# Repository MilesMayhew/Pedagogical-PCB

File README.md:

# Project Title

A brief description of what this project does and who it's for.

## Table of Contents

- [Introduction](#introduction)
- [Installation](#installation)
- [Usage](#usage)
- [Technology Stack](#technology-stack)

## Introduction
The goal of this project is to develop hardware to facilitate a new learning environment for use in ECE3430 (Introduction to Embedded Computer Systems). The board will support the use of two widely used development boards, the STM32 development board and the TI MSPM0 development board, and contain a number of auxiliary I/O that can be used to develop learning activities to learn how to interface to digital I/O, analog I/O, and serial I/O. This includes a complete hardware design and software solutions for specific implementations of learning activities using specific I/O 
## Usage
- **STM32**
  - For each of the provided software solutions: Open STM32CubeIDE and imp# Bill of Materials (BOM)

## Overview

A comprehensive list of all the components required for the project, including specifications and sourcing information.

## Table of Contents

- [Components](#components)
- [Tools Required](#tools-required)
- [Notes](#notes)

## Components

| Item No | Component              | Quantity | Description                   | Supplier/Source         | Part Number       | Price      |
|---------|-----------------------|----------|-------------------------------|-------------------------|-------------------|------------|
| 1       | Resistor              | 10       | 220 Ohm, 1/4 Watt, 5% Tolerance | [Digi-Key](https://www.digikey.com/) | 220R-1/4W-5%       | $0.10     |
| 2       | Capacitor             | 5        | 100 µF, 16V Electrolytic     | [Mouser](https://www.mouser.com/) | 100uF-16V        | $0.25     |
| 3       | Microcontroller       | 1        | ATmega328P                    | [SparkFun](https://www.sparkfun.com/) | ATMEGA328P         | $2.50     |
| 4       | PCB                   | 1        | Custom PCB                    | [JLCPCB](https://www.jlcpcb.com/) | CustomPCB-XYZ      | $3.00     |
| 5       | KiCad Software        | 1        | PCB Design Software           | [KiCad](https://www.kicad.org/) | N/A                 | Free       |

## Tools Required

- Soldering Iron
- Wire Cutters
- Multimeter
- Screwdriver Set

## Notes

- Ensure all components meet the specified requirements.
- Check for component availability and potential substitutions.
ort file as new project. Flash to STM32 development board, and connect correct IO to hardware pins as documented in solution.

## Installation

1. Clone the repository:
   ```bash
   git clone https://github.com/MilesMayhew/Pedagogical-PCB.git
## Technology Stack

- **Languages**: 
  - C
- **Boards**
  - STM32 nucleo
  - TI LP-MSPMOG3507
- **Tools / Libraries**:
  - Git
  - STM32CubeIDE 1.16.0
  - Code Composer Studio
- **Hardware Design**:
  - KiCad

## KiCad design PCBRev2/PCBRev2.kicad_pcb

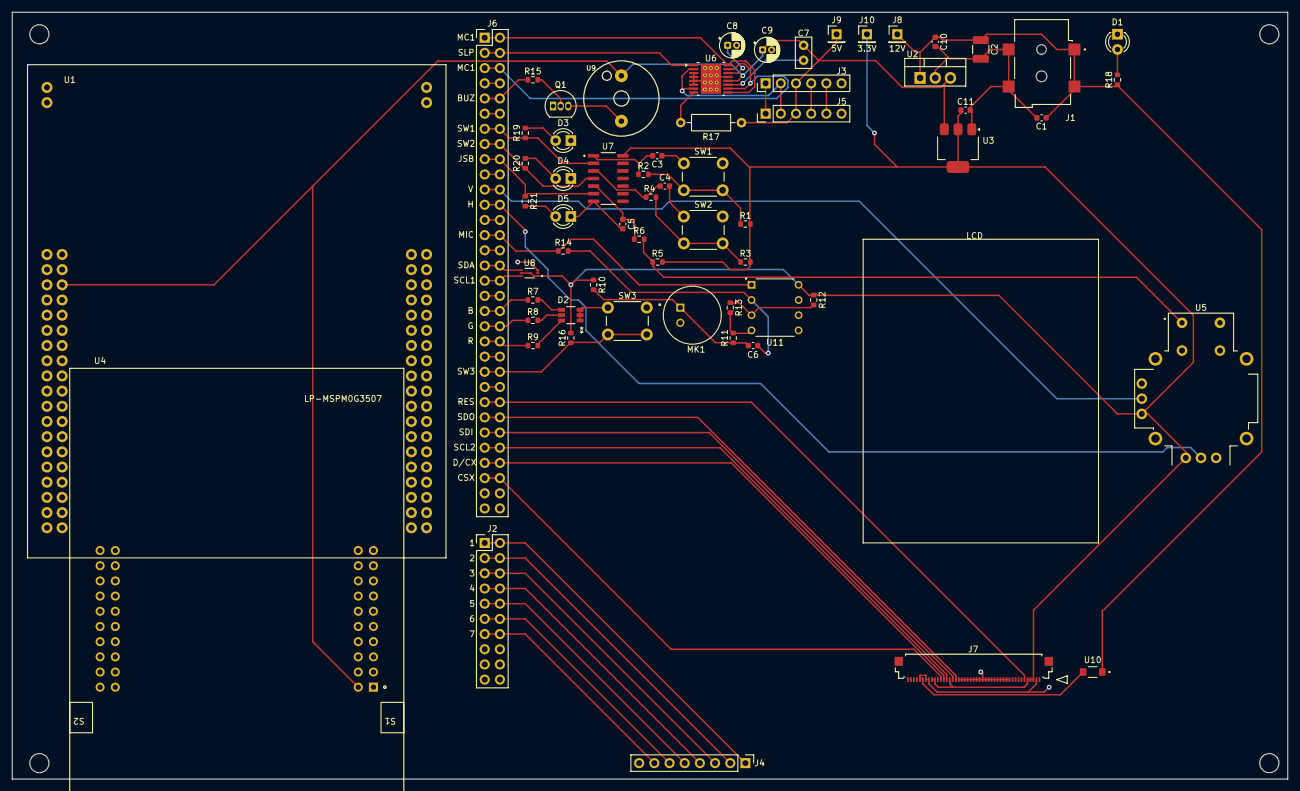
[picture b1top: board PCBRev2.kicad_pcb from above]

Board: 2 copper layers, 213.4 x 128.3 mm, 63 parts (0 on the bottom side), 68 nets.

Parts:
C1: 0.1uf; C_0603_1608Metric
C2: 47uf; C_1210_3225Metric_Pad1.33x2.70mm_HandSolder
C3, C4, C5: 0.47uF; C_0603_1608Metric
C6: 1 uF; C_0603_1608Metric
C7: 0.01 uF; C_Disc_D5.0mm_W2.5mm_P2.50mm
C8: 2.2uF; CP_Radial_D4.0mm_P1.50mm
C9: 10UF; CP_Radial_D4.0mm_P1.50mm
C10: 0.22uf; C_0603_1608Metric
C11: 1uf; C_0603_1608Metric
D1, D3, D4, D5: LED; LED_D3.0mm_FlatTop
D2: AAAF3529LSEEZGKQBKS; LED_AAAF3529LSEEZGKQBKS_KNB
J1: 54-00164; TENSILITY_54-00164
J2: Conn_02x10_Odd_Even; PinHeader_2x10_P2.54mm_Vertical
J3, J5: PinHeader_1x06_P2.54mm_Vertical
J4: Keypad; PinHeader_1x08_P2.54mm_Vertical
J6: Conn_02x30_Odd_Even; PinHeader_2x32_P2.54mm_Vertical
J7: 512964594; CON_512964594_MOL
J8: 12V; PinHeader_1x01_P2.54mm_Vertical
J9: 5V; PinHeader_1x01_P2.54mm_Vertical
J10: 3.3V; PinHeader_1x01_P2.54mm_Vertical
MK1: CMA-4544PF-W; MIC_CMA-4544PF-W
Q1: 2N4401; TO-92_Inline
R1, R2, R3, R4, R5, R6, R16: 10kR; R_0603_1608Metric
R7, R8: 300; R_0603_1608Metric
R9: 750; R_0603_1608Metric
R10, R11, R12, R13: 2.2kR; R_0603_1608Metric
R14: 68k; R_0603_1608Metric
R15: 620; R_0603_1608Metric
R17: 10K; R_Axial_DIN0207_L6.3mm_D2.5mm_P10.16mm_Horizontal
R18: 510; R_0603_1608Metric
R19, R20: 68; R_0603_1608Metric
R21: 330; R_0603_1608Metric
SW1, SW2, SW3: SW_Push; SW_PUSH_6mm_H7.3mm
U1: NUCLEO-G0B1RE; MODULE_NUCLEO-G0B1RE
U2: LM7805_TO220; TO-220-3_Vertical
U3: TLV1117-33; SOT-223-3_TabPin2
U4: LP-MSPM0G3507; ti_LP_MSPM0G3507
U5: COM-09032; XDCR_COM-09032
U6: DRV8833PWP; HTSSOP-16-1EP_4.4x5mm_P0.65mm_EP3.4x5mm_Mask2.46x2.31mm_The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
U7: SN74AHCT14QDRG4Q1; SOIC127P600X175-14N
U8: BH1750FVI-TR; XDCR_BH1750FVI-TR
U9: WST-1205S
U10: AL5809-20QP1-7; SODFL3717X100N
U11: MCP6002-I_P; DIP787W46P254L927H533Q8

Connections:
+5V: C7.1, C9.1, J3.3 (Tach_Power), J5.3 (Tach_Power), J9.1, R17.1, U1.CN7_6 (E5V), U2.3 (VO), U3.3 (VI), U4.J3_1 (+VBUS), U6.12 (VM), U9.+
+12V: C1.1, C2.1, C10.1, J1.A1, J1.A2, J8.1, R18.1, U2.1 (VI), U10.1 (IN)
/Button1 Input: R1.1, R2.2, SW1.2
/Button2 Input: R3.1, R4.2, SW2.2
/Motor_Drive_1: J3.2 (Fan_1), J5.2 (Fan_1), U6.2 (AOUT1), U6.7 (BOUT1)
/Tach_Out_1: J3.4 (Tach_Out_1), J5.4 (Tach_Out_1)
/Tach_Out_2: J3.5 (Tach_Out_2), J5.5 (Tach_Out_2)
/_Motor_Fault: R17.2, U6.8 (~FAULT)
B: J6.37, J6.38, R7.1
ButtonNoDebounce: J6.45, J6.46, R16.1, SW3.2
BuzzerGPIO: J6.9, J6.10, R15.1
CSX: J6.59, J6.60, J7.34
D/CX: J6.57, J6.58, J7.33
G: J6.39, J6.40, R8.1
GNDREF: C1.2, C2.2, C3.1, C4.2, C5.2, C8.2, C9.2, C10.2, C11.2, D1.1 (K), D2.1, D2.2, D2.3, D3.1 (K), D4.1 (K), D5.1 (K), J1.B, J1.C, J3.1 (Fan_2), J3.6 (Tach_GND), J5.1 (Fan_2), J5.6 (Tach_GND), J7.2, J7.11, J7.12, J7.13, J7.14, J7.15, J7.16, J7.17, J7.18, J7.19, J7.20, J7.21, J7.22, J7.23, J7.24, J7.25, J7.26, J7.27, J7.28, J7.38, J7.39, J7.41, MK1.2, Q1.1 (S), R11.2, R13.2, SW1.1, SW2.1, SW3.1, U1.CN7_8 (GND), U1.CN7_19 (GND), U1.CN7_20 (GND), U1.CN7_22 (GND), U1.CN10_20 (GND), U1.JP4_1 (GND), U1.JP4_2 (GND), U1.JP5_1 (GND), U1.JP5_2 (GND), U2.2 (GND), U3.1 (GND), U4.J3_2 (GND), U5.B2A (SEL-), U5.H3 (H-), U5.S1 (SHIELD), U5.S2 (SHIELD), U5.S3 (SHIELD), U5.S4 (SHIELD), U5.V3 (V-), U6.3 (AISEN), U6.4 (AOUT2), U6.5 (BOUT2), U6.6 (BISEN), U6.13 (GND), U6.17 (GND), U7.7 (GND), U8.2 (ADDR), U8.3 (GND), U11.4 (VSS)
H: J6.23, J6.24, U5.H2 (H)
JSB: J6.17, J6.18, R21.1, U7.6 (3Y)
MicOut: J6.27, J6.28, R14.1, U11.1 (VOUTA)
MotorControl1: J6.1, J6.2, U6.9 (BIN1), U6.16 (AIN1)
MotorControl2: J6.5, J6.6, U6.10 (BIN2), U6.15 (AIN2)
Motor_Sleep: J6.3, J6.4, U6.1 (~SLEEP)
unnamed: C6.1, MK1.1, R10.2, R11.1
unnamed: D1.2 (A), R18.2
unnamed: D2.4, R7.2
unnamed: D2.5, R8.2
unnamed: D2.6, R9.2
unnamed: D3.2 (A), R19.2
unnamed: D4.2 (A), R20.2
unnamed: D5.2 (A), R21.2
unnamed: J2.1, J2.2, J4.1
unnamed: J2.3, J2.4, J4.2
unnamed: J2.5, J2.6, J4.3
unnamed: J2.7, J2.8, J4.4
unnamed: J2.9, J2.10, J4.5
unnamed: J2.11, J2.12, J4.6
unnamed: J2.13, J2.14, J4.7
unnamed: J6.7, J6.8
unnamed: J6.11, J6.12
unnamed: J6.19, J6.20
unnamed: J6.25, J6.26
unnamed: J6.29, J6.30
unnamed: J6.35, J6.36
unnamed: J6.43, J6.44
unnamed: J6.47, J6.48
unnamed: Q1.3 (D), U9.-
unnamed: Q1.2 (G), R15.2
unnamed: U1.CN7_12 (3V3), U1.CN7_16 (3V3)
unnamed: U1.CN10_9 (AGND), U1.CN10_32 (AGND)
unnamed: R5.1, R6.2, U5.B1A (SEL+)
unnamed: C7.2, U6.11 (VCP)
unnamed: C8.1, U6.14 (VINT)
unnamed: C3.2, R2.1, U7.1 (1A)
unnamed: C4.1, R4.1, U7.3 (2A)
unnamed: C5.1, R6.1, U7.5 (3A)
unnamed: J7.40, U10.2 (OUT)
unnamed: R12.2, R13.1, U11.3 (VINA+)
unnamed: C6.2, R14.2, U11.2 (VINA-)
R: J6.41, J6.42, R9.1
RESX: J6.49, J6.50, J7.6
SCL: J6.55, J6.56, J7.32
SCLlight: J6.33, J6.34, U8.6 (SCL)
SDA: J6.31, J6.32, U8.4 (SDA)
SDI: J6.53, J6.54, J7.30
SDO: J6.51, J6.52, J7.29
SW1: J6.13, J6.14, R19.1, U7.2 (1Y)
SW2: J6.15, J6.16, R20.1, U7.4 (2Y)
V: J6.21, J6.22, U5.V2 (V)
VDD: C11.1, J7.3, J7.4, J7.5, J7.31, J7.36, J7.37, J10.1, R1.2, R3.2, R5.2, R10.1, R12.1, R16.2, U3.2 (VO), U5.H1 (H+), U5.V1 (V+), U7.14 (VCC), U8.1 (VCC), U8.5 (DVI), U11.8 (VDD)

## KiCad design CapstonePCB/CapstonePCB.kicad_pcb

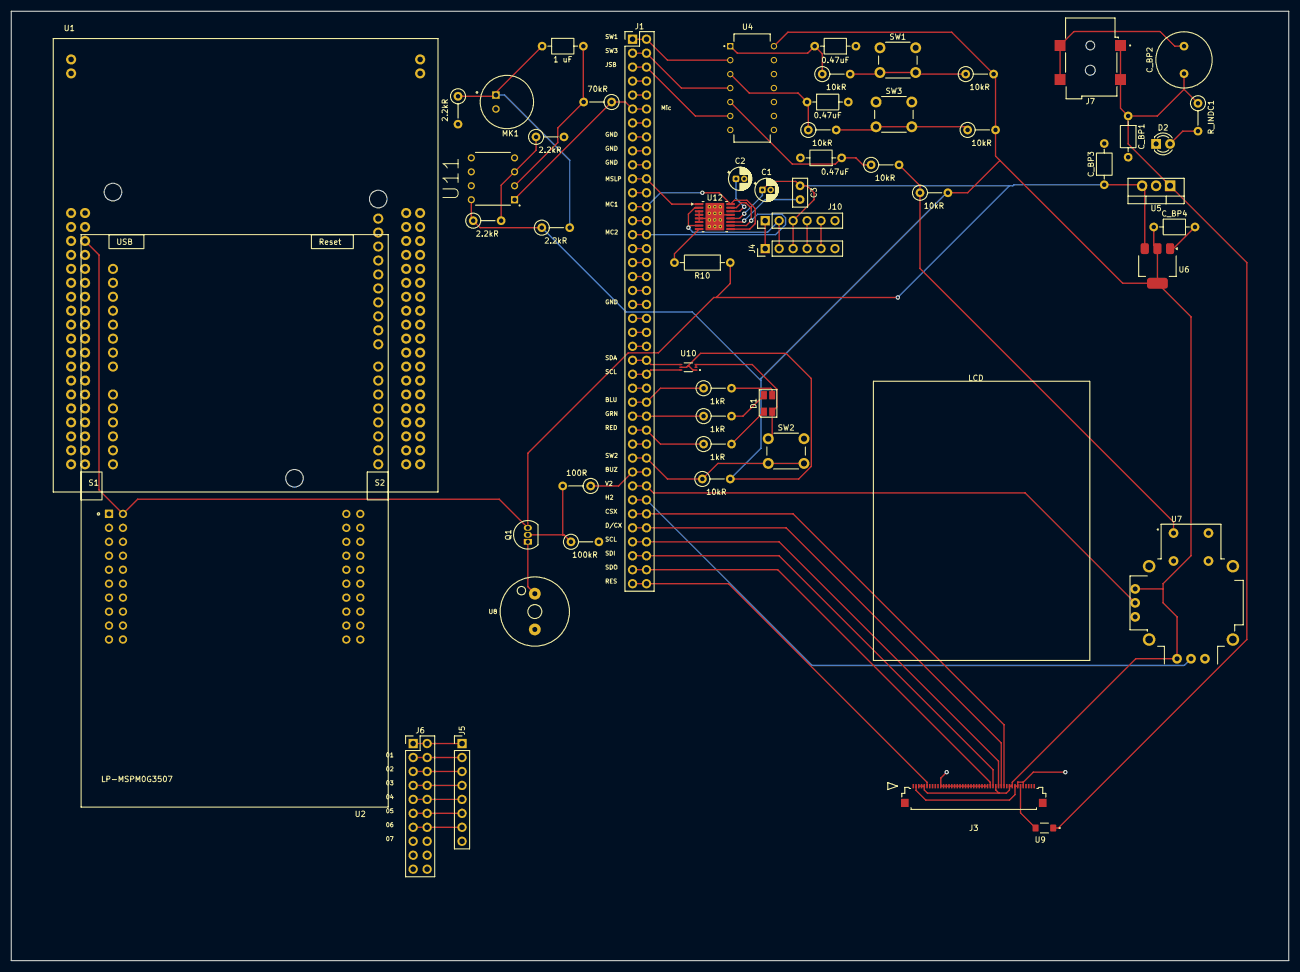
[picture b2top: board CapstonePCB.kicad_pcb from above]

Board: 2 copper layers, 232.4 x 172.7 mm, 55 parts (0 on the bottom side), 93 nets.

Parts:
C1: 10UF; CP_Radial_D4.0mm_P1.50mm
C2: 2.2uF; CP_Radial_D4.0mm_P1.50mm
C3: 0.01 uF; C_Disc_D5.0mm_W2.5mm_P2.50mm
CJS1: 0.47uF; C_Axial_L3.8mm_D2.6mm_P7.50mm_Horizontal
CSW1, CSW3: 0.47uF; C_Axial_L3.8mm_D2.6mm_P7.50mm_Horizontal
C_BP1: 0.1 uf; C_Axial_L3.8mm_D2.6mm_P7.50mm_Horizontal
C_BP2: 47 uf; C_Radial_D10.0mm_H20.0mm_P5.00mm
C_BP3, C_BP4: 100 uf; C_Axial_L3.8mm_D2.6mm_P7.50mm_Horizontal
C_s2: 1 uF; C_Axial_L3.8mm_D2.6mm_P7.50mm_Horizontal
D1: ASMB-MTB1-0A3A2; LED_Avago_PLCC4_3.2x2.8mm_CW
D2: LED; LED_D3.0mm_FlatTop
J1: Conn_02x40_Counter_Clockwise; PinHeader_2x40_P2.54mm_Vertical
J3: 512964594; CON_512964594_MOL
J4, J10: PinHeader_1x06_P2.54mm_Vertical
J5: Keypad; PinHeader_1x08_P2.54mm_Vertical
J6: Conn_02x10_Odd_Even; PinHeader_2x10_P2.54mm_Vertical
J7: 54-00164; TENSILITY_54-00164
MK1: CMA-4544PF-W; MIC_CMA-4544PF-W
PullUpResistor2: 10kR; R_Axial_DIN0207_L6.3mm_D2.5mm_P5.08mm_Vertical
PullUpResistorJS1: 10kR; R_Axial_DIN0207_L6.3mm_D2.5mm_P5.08mm_Vertical
PullUpResistorSW1, PullUpResistorSW3: 10kR; R_Axial_DIN0207_L6.3mm_D2.5mm_P5.08mm_Vertical
Q1: 2N7000; TO-92_Inline
R10: 10K; R_Axial_DIN0207_L6.3mm_D2.5mm_P10.16mm_Horizontal
RJS1: 10kR; R_Axial_DIN0207_L6.3mm_D2.5mm_P5.08mm_Vertical
RSW1, RSW3: 10kR; R_Axial_DIN0207_L6.3mm_D2.5mm_P5.08mm_Vertical
R_BUZ1: 100R; R_Axial_DIN0207_L6.3mm_D2.5mm_P5.08mm_Vertical
R_BUZ2: 100kR; R_Axial_DIN0207_L6.3mm_D2.5mm_P5.08mm_Vertical
R_COFF2, R_COFF3, R_COFF4: 1kR; R_Axial_DIN0207_L6.3mm_D2.5mm_P5.08mm_Vertical
R_INDC1: 5.5k ohm; R_Axial_DIN0207_L6.3mm_D2.5mm_P5.08mm_Vertical
R_SNSA2, R_SNSA3, R_SNSA5, R_SNSA6: 2.2kR; R_Axial_DIN0207_L6.3mm_D2.5mm_P5.08mm_Vertical
R_SNSA4: 70kR; R_Axial_DIN0207_L6.3mm_D2.5mm_P5.08mm_Vertical
SW1, SW2, SW3: SW_Push; SW_PUSH_6mm_H7.3mm
U1: NUCLEO-G0B1RE; MODULE_NUCLEO-G0B1RE
U2: LP-MSPM0G3507; ti_LP_MSPM0G3507
U4: SN74AHC14N; DIP794W45P254L1969H508Q14
U5: LM7805_TO220; TO-220-3_Vertical
U6: TLV1117-33; SOT-223-3_TabPin2
U7: COM-09032; XDCR_COM-09032
U8: WST-1205S
U9: AL5809-20QP1-7; SODFL3717X100N
U10: BH1750FVI-TR; XDCR_BH1750FVI-TR
U11: MCP6002-I_P; DIP787W46P254L927H533Q8
U12: DRV8833PWP; HTSSOP-16-1EP_4.4x5mm_P0.65mm_EP3.4x5mm_Mask2.46x2.31mm_The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

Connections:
+3.3V: U1.CN6_2 (3V3), U1.CN6_4 (3V3), U1.CN7_12 (3V3), U1.CN7_16 (3V3)
+5V: C1.1, C3.1, C_BP3.1, J4.3 (Tach_Power), J10.3 (Tach_Power), Q1.3 (D), R10.1, U1.CN7_6 (E5V), U2.J3_1 (+VBUS), U5.3 (VO), U6.3 (VI), U12.12 (VM)
+12V: C_BP1.1, C_BP2.1, J7.A1, J7.A2, R_INDC1.1, U5.1 (VI), U9.1 (IN)
/Button1 Input: PullUpResistorSW1.1, RSW1.2, SW1.2
/Button2 Input: PullUpResistorSW3.1, RSW3.2, SW3.2
/Button No Debouning: J1.61, J1.62, PullUpResistor2.1, SW2.2
/Motor_Drive_1: J4.2 (Fan_1), J10.2 (Fan_1), U12.2 (AOUT1), U12.7 (BOUT1)
/Tach_Out_1: J4.4 (Tach_Out_1), J10.4 (Tach_Out_1)
/Tach_Out_2: J4.5 (Tach_Out_2), J10.5 (Tach_Out_2)
/_Motor_Fault: R10.2, U12.8 (~FAULT)
BuzzerGPIO: J1.63, J1.64, R_BUZ1.1
GNDREF: C1.2, C2.2, CJS1.2, CSW1.1, CSW3.2, C_BP1.2, C_BP2.2, C_BP3.2, C_BP4.2, D1.4 (A), D2.1 (K), J1.15, J1.16, J1.17, J1.18, J1.19, J1.20, J1.27, J1.28, J1.39, J1.40, J3.2, J3.11, J3.12, J3.13, J3.14, J3.15, J3.16, J3.17, J3.18, J3.19, J3.20, J3.21, J3.22, J3.23, J3.24, J3.25, J3.26, J3.27, J3.28, J3.38, J3.39, J3.41, J4.1 (Fan_2), J4.6 (Tach_GND), J7.B, J7.C, J10.1 (Fan_2), J10.6 (Tach_GND), MK1.2, R_BUZ2.2, R_SNSA3.2, R_SNSA6.2, SW1.1, SW2.1, SW3.1, U1.CN6_6 (GND), U1.CN6_7 (GND), U1.CN7_8 (GND), U1.CN7_19 (GND), U1.CN7_20 (GND), U1.CN7_22 (GND), U1.CN10_20 (GND), U1.JP4_1 (GND), U1.JP4_2 (GND), U1.JP5_1 (GND), U1.JP5_2 (GND), U2.J3_2 (GND), U4.7 (GND), U5.2 (GND), U6.1 (GND), U7.B2A (SEL-), U7.H3 (H-), U7.S1 (SHIELD), U7.S2 (SHIELD), U7.S3 (SHIELD), U7.S4 (SHIELD), U7.V3 (V-), U8.-, U10.2 (ADDR), U10.3 (GND), U11.4 (VSS), U12.3 (AISEN), U12.4 (AOUT2), U12.5 (BOUT2), U12.6 (BISEN), U12.13 (GND), U12.17 (GND)
MicOut: J1.11, J1.12, R_SNSA4.1, U11.1 (VOUTA)
MotorControl1: J1.25, J1.26, U12.9 (BIN1), U12.16 (AIN1)
MotorControl2: J1.29, J1.30, U12.10 (BIN2), U12.15 (AIN2)
Motor_Sleep: J1.21, J1.22, U12.1 (~SLEEP)
unnamed: C_s2.1, MK1.1, R_SNSA2.2, R_SNSA3.1
unnamed: D1.3 (BK), R_COFF4.2
unnamed: D1.2 (GK), R_COFF3.2
unnamed: D1.1 (RK), R_COFF2.2
unnamed: D2.2 (A), R_INDC1.2
unnamed: J1.1, J1.2, U4.2 (1Y)
unnamed: J1.3, J1.4, U4.4 (2Y)
unnamed: J1.5, J1.6, U4.6 (3Y)
unnamed: J1.7, J1.8
unnamed: J1.9, J1.10
unnamed: J1.13, J1.14
unnamed: J1.23, J1.24
unnamed: J1.31, J1.32
unnamed: J1.33, J1.34
unnamed: J1.35, J1.36
unnamed: J1.37, J1.38
unnamed: J1.41, J1.42
unnamed: J1.43, J1.44
unnamed: J1.45, J1.46
unnamed: J1.47, J1.48, U10.4 (SDA)
unnamed: J1.49, J1.50, U10.6 (SCL)
unnamed: J1.51, J1.52
unnamed: J1.53, J1.54, R_COFF4.1
unnamed: J1.55, J1.56, R_COFF3.1
unnamed: J1.57, J1.58, R_COFF2.1
unnamed: J1.59, J1.60
unnamed: J1.65, J1.66, U7.V2 (V)
unnamed: J1.67, J1.68, U7.H2 (H)
unnamed: J1.69, J1.70, J3.34
unnamed: J1.71, J1.72, J3.33
unnamed: J1.73, J1.74, J3.32
unnamed: J1.75, J1.76, J3.30
unnamed: J1.77, J1.78, J3.29
unnamed: J1.79, J1.80, J3.6
unnamed: J5.1, J6.1, J6.2
unnamed: J5.2, J6.3, J6.4
unnamed: J5.3, J6.5, J6.6
unnamed: J5.4, J6.7, J6.8
unnamed: J5.5, J6.9, J6.10
unnamed: J5.6, J6.11, J6.12
unnamed: J5.7, J6.13, J6.14
unnamed: Q1.2 (G), R_BUZ1.2, R_BUZ2.1
unnamed: Q1.1 (S), U8.+
unnamed: U1.CN7_28 (PA0), U1.CN8_1 (PA0)
unnamed: U1.CN7_30 (PA1), U1.CN8_2 (PA1)
unnamed: U1.CN7_32 (PA4), U1.CN8_3 (PA4)
unnamed: U1.CN5_6 (PA5), U1.CN10_11 (PA5)
unnamed: U1.CN5_5 (PA6), U1.CN10_13 (PA6)
unnamed: U1.CN5_4 (PA7), U1.CN10_15 (PA7)
unnamed: U1.CN9_8 (PA8), U1.CN10_23 (PA8)
unnamed: U1.CN5_1 (PA9), U1.CN10_21 (PA9)
unnamed: U1.CN9_3 (PA10), U1.CN10_33 (PA10)
unnamed: U1.CN5_3 (PB0), U1.CN10_17 (PB0)
unnamed: U1.CN7_34 (PB1), U1.CN8_4 (PB1)
unnamed: U1.CN9_4 (PB3), U1.CN10_31 (PB3)
unnamed: U1.CN9_6 (PB4), U1.CN10_27 (PB4)
unnamed: U1.CN9_5 (PB5), U1.CN10_29 (PB5)
unnamed: U1.CN5_10 (PB8), U1.CN10_3 (PB8)
unnamed: U1.CN5_9 (PB9), U1.CN10_5 (PB9)
unnamed: U1.CN9_7 (PB14), U1.CN10_25 (PB14)
unnamed: U1.CN9_2 (PC4), U1.CN10_35 (PC4)
unnamed: U1.CN9_1 (PC5), U1.CN10_37 (PC5)
unnamed: U1.CN5_2 (PC7), U1.CN10_19 (PC7)
unnamed: U1.CN6_3 (~RST), U1.CN7_14 (~RST)
unnamed: U1.CN6_5 (5V), U1.CN7_18 (5V)
unnamed: U1.CN5_7 (AGND), U1.CN10_9 (AGND), U1.CN10_32 (AGND)
unnamed: U1.CN6_8 (VIN), U1.CN7_24 (VIN)
unnamed: CSW1.2, RSW1.1, U4.1 (1A)
unnamed: CSW3.1, RSW3.1, U4.3 (2A)
unnamed: CJS1.1, RJS1.1, U4.5 (3A)
unnamed: PullUpResistorJS1.1, RJS1.2, U7.B1A (SEL+)
unnamed: J3.40, U9.2 (OUT)
unnamed: R_SNSA5.2, R_SNSA6.1, U11.3 (VINA+)
unnamed: C_s2.2, R_SNSA4.2, U11.2 (VINA-)
unnamed: C3.2, U12.11 (VCP)
unnamed: C2.1, U12.14 (VINT)
VDD: C_BP4.1, J3.3, J3.4, J3.5, J3.31, J3.36, J3.37, PullUpResistor2.2, PullUpResistorJS1.2, PullUpResistorSW1.2, PullUpResistorSW3.2, R_SNSA2.1, R_SNSA5.1, U4.14 (VCC), U6.2 (VO), U7.H1 (H+), U7.V1 (V+), U10.1 (VCC), U10.5 (DVI), U11.8 (VDD)

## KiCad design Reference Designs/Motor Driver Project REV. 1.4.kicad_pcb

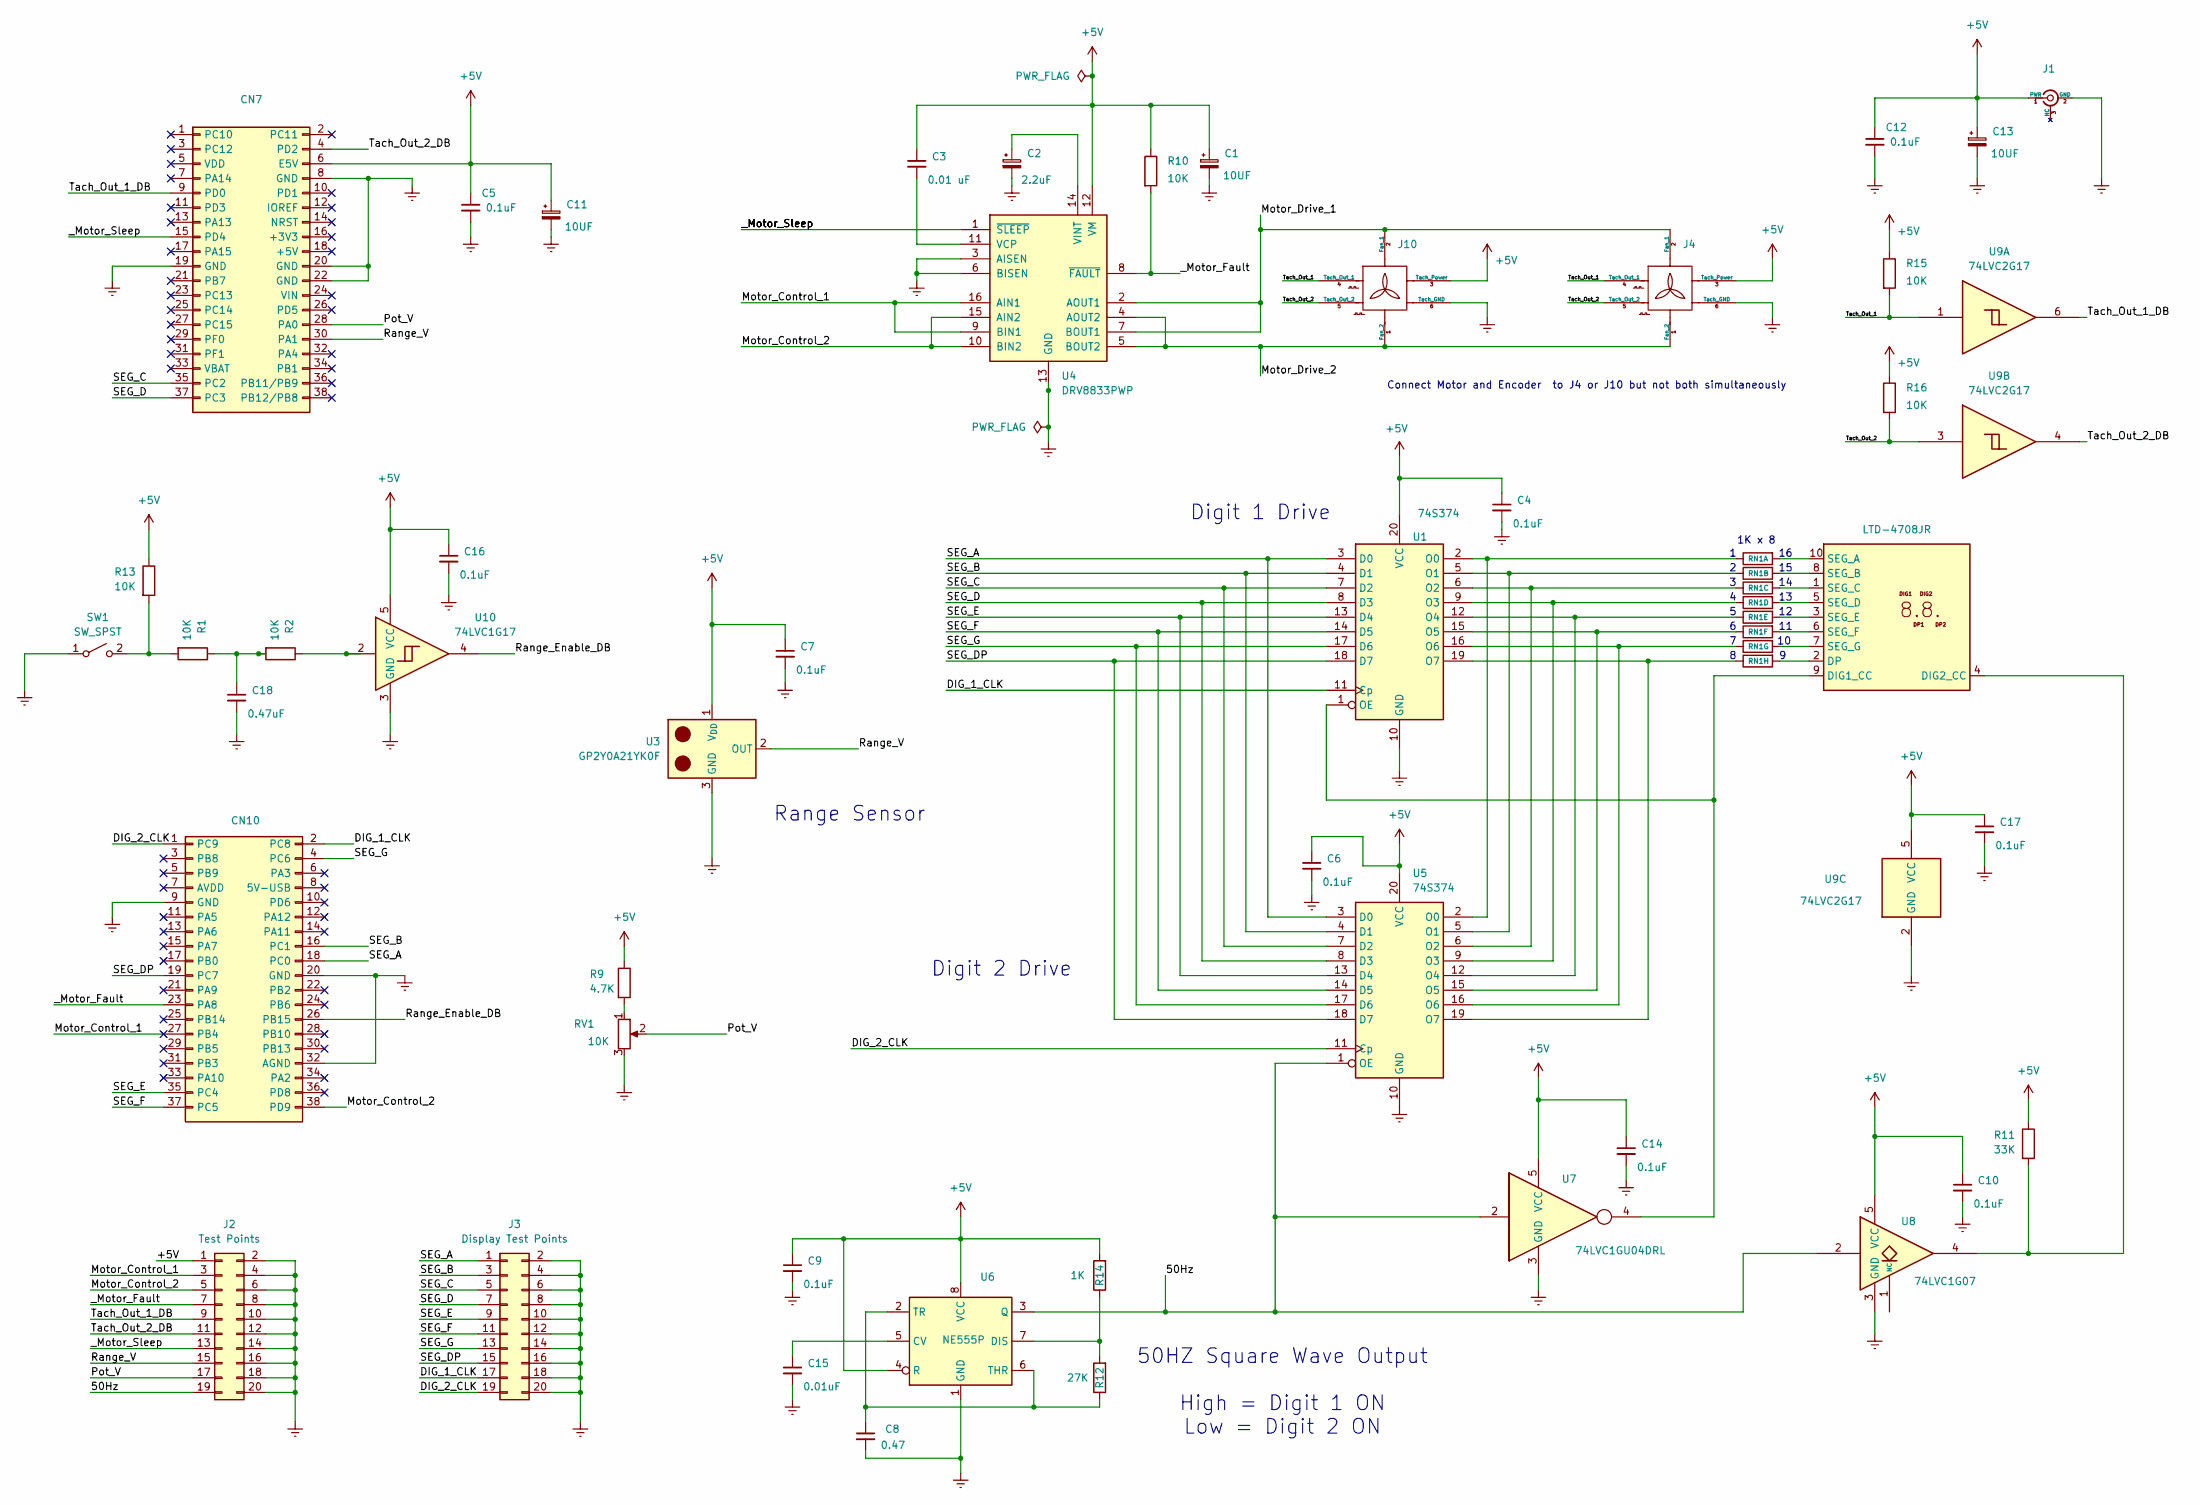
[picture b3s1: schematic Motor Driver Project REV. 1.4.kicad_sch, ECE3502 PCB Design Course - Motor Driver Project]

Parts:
C1, C11, C13: 10UF; CP_Radial_D4.0mm_P1.50mm
C2: 2.2uF; CP_Radial_D4.0mm_P1.50mm
C3: 0.01 uF; C_Disc_D5.0mm_W2.5mm_P2.50mm
C4, C5, C6, C7, C9, C10, C12, C14, C16, C17: 0.1uF; C_Disc_D5.0mm_W2.5mm_P2.50mm
C8: 0.47; C_Disc_D5.0mm_W2.5mm_P2.50mm
C15: 0.01uF; C_Disc_D5.0mm_W2.5mm_P2.50mm
C18: 0.47uF; C_Disc_D5.0mm_W2.5mm_P2.50mm
CN7: Conn_2Rows-38Pins_CN7; PinSocket_2x19_P2.54mm_Vertical_CN7
CN10: Conn_2Rows-38Pins_CN10; PinSocket_2x19_P2.54mm_Vertical_CN10
J1: Conn_Coaxial_3_Pin; BarrelJack_GCT_DCJ200-10-A_Horizontal
J2: Test Points; PinHeader_2x10_P2.54mm_Vertical
J3: Display Test Points; PinHeader_2x10_P2.54mm_Vertical
J4, J10: PinHeader_1x06_P2.54mm_Vertical
R1, R2, R10, R13, R15, R16: 10K; R_Axial_DIN0207_L6.3mm_D2.5mm_P10.16mm_Horizontal
R9: 4.7K; R_Axial_DIN0207_L6.3mm_D2.5mm_P10.16mm_Horizontal
R11: 33K; R_Axial_DIN0207_L6.3mm_D2.5mm_P10.16mm_Horizontal
R12: 27K; R_Axial_DIN0207_L6.3mm_D2.5mm_P10.16mm_Horizontal
R14: 1K; R_Axial_DIN0207_L6.3mm_D2.5mm_P10.16mm_Horizontal
RN1: R_Pack08_Split; DIP-16_W7.62mm
RV1: 10K; TRIM_COM-09806
SW1: SW_SPST; SW2_GF-123-0054_CWI
U1, U5: 74S374; DIP-20_W7.62mm_Socket
U2: LTD-4708JR; 7SegmentLED_LTD-4708JR
U3: GP2Y0A21YK0F; PinHeader_1x03_P2.54mm_Vertical
U4: DRV8833PWP; HTSSOP-16-1EP_4.4x5mm_P0.65mm_EP3.4x5mm_Mask2.46x2.31mm_The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
U6: NE555P; DIP-8_W7.62mm
U7: 74LVC1GU04DRL; SOT-23-5_HandSoldering
U8: 74LVC1G07; SOT-23-5_HandSoldering
U9: 74LVC2G17; SOT-23-6
U10: 74LVC1G17; SOT-23-5

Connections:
+5V: C1.1, C3.1, C4.1, C5.1, C6.1, C7.1, C9.1, C10.1, C11.1, C12.1, C13.1, C14.1, C16.1, C17.1, CN7.6 (E5V), J1.1 (PWR), J2.1, J4.3 (Tach_Power), J10.3 (Tach_Power), R9.1, R10.1, R11.1, R13.1, R14.2, R15.1, R16.1, U1.20 (VCC), U3.1 (V_{DD}), U4.12 (VM), U5.20 (VCC), U6.4 (R), U6.8 (VCC), U7.5 (VCC), U8.5 (VCC), U9.5 (VCC), U10.5 (VCC)
/50Hz: J2.19, U5.1 (OE), U6.3 (Q), U7.2, U8.2
/DIG_1_CLK: CN10.2 (PC8), J3.17, U1.11 (Cp)
/DIG_2_CLK: CN10.1 (PC9), J3.19, U5.11 (Cp)
/Motor_Control_1: CN10.27 (PB4), J2.3, U4.9 (BIN1), U4.16 (AIN1)
/Motor_Control_2: CN10.38 (PD9), J2.5, U4.10 (BIN2), U4.15 (AIN2)
/Motor_Drive_1: J4.2 (Fan_1), J10.2 (Fan_1), U4.2 (AOUT1), U4.7 (BOUT1)
/Motor_Drive_2: J4.1 (Fan_2), J10.1 (Fan_2), U4.4 (AOUT2), U4.5 (BOUT2)
/Pot_V: CN7.28 (PA0), J2.17, RV1.2
/Range_Enable_DB: CN10.26 (PB15), U10.4
/Range_V: CN7.30 (PA1), J2.15, U3.2 (OUT)
/SEG_A: CN10.18 (PC0), J3.1, U1.3 (D0), U5.3 (D0)
/SEG_B: CN10.16 (PC1), J3.3, U1.4 (D1), U5.4 (D1)
/SEG_C: CN7.35 (PC2), J3.5, U1.7 (D2), U5.7 (D2)
/SEG_D: CN7.37 (PC3), J3.7, U1.8 (D3), U5.8 (D3)
/SEG_DP: CN10.19 (PC7), J3.15, U1.18 (D7), U5.18 (D7)
/SEG_E: CN10.35 (PC4), J3.9, U1.13 (D4), U5.13 (D4)
/SEG_F: CN10.37 (PC5), J3.11, U1.14 (D5), U5.14 (D5)
/SEG_G: CN10.4 (PC6), J3.13, U1.17 (D6), U5.17 (D6)
/Tach_Out_1: J4.4 (Tach_Out_1), J10.4 (Tach_Out_1), R15.2, U9.1
/Tach_Out_1_DB: CN7.9 (PD0), J2.9, U9.6
/Tach_Out_2: J4.5 (Tach_Out_2), J10.5 (Tach_Out_2), R16.2, U9.3
/Tach_Out_2_DB: CN7.4 (PD2), J2.11, U9.4
/_Motor_Fault: CN10.23 (PA8), J2.7, R10.2, U4.8 (~FAULT)
/_Motor_Sleep: CN7.15 (PD4), J2.13, U4.1 (~SLEEP)
Earth: C1.2, C2.2, C4.2, C5.2, C6.2, C7.2, C8.2, C9.2, C10.2, C11.2, C12.2, C13.2, C14.2, C15.2, C16.2, C17.2, C18.2, CN7.8 (GND), CN7.19 (GND), CN7.20 (GND), CN7.22 (GND), CN10.9 (GND), CN10.20 (GND), CN10.32 (AGND), J1.2 (GND), J2.2, J2.4, J2.6, J2.8, J2.10, J2.12, J2.14, J2.16, J2.18, J2.20, J3.2, J3.4, J3.6, J3.8, J3.10, J3.12, J3.14, J3.16, J3.18, J3.20, J4.6 (Tach_GND), J10.6 (Tach_GND), RV1.3, SW1.1 (A), U1.10 (GND), U3.3 (GND), U4.3 (AISEN), U4.6 (BISEN), U4.13 (GND), U4.17 (GND), U5.10 (GND), U6.1 (GND), U7.3 (GND), U8.3 (GND), U9.2 (GND), U10.3 (GND)
unnamed: C18.1, R1.1, R2.2
unnamed: R2.1, U10.2
unnamed: R9.2, RV1.1
unnamed: RN1.1 (R1.1), U1.2 (O0), U5.2 (O0)
unnamed: RN1.16 (R1.2), U2.10 (SEG_A)
unnamed: RN1.2 (R2.1), U1.5 (O1), U5.5 (O1)
unnamed: RN1.15 (R2.2), U2.8 (SEG_B)
unnamed: RN1.3 (R3.1), U1.6 (O2), U5.6 (O2)
unnamed: RN1.14 (R3.2), U2.1 (SEG_C)
unnamed: RN1.4 (R4.1), U1.9 (O3), U5.9 (O3)
unnamed: RN1.13 (R4.2), U2.5 (SEG_D)
unnamed: RN1.5 (R5.1), U1.12 (O4), U5.12 (O4)
unnamed: RN1.12 (R5.2), U2.3 (SEG_E)
unnamed: RN1.6 (R6.1), U1.15 (O5), U5.15 (O5)
unnamed: RN1.11 (R6.2), U2.6 (SEG_F)
unnamed: RN1.7 (R7.1), U1.16 (O6), U5.16 (O6)
unnamed: RN1.10 (R7.2), U2.7 (SEG_G)
unnamed: RN1.8 (R8.1), U1.19 (O7), U5.19 (O7)
unnamed: RN1.9 (R8.2), U2.2 (DP)
unnamed: R1.2, R13.2, SW1.2 (B)
unnamed: U1.1 (OE), U2.9 (DIG1_CC), U7.4
unnamed: R11.2, U2.4 (DIG2_CC), U8.4
unnamed: C3.2, U4.11 (VCP)
unnamed: C2.1, U4.14 (VINT)
unnamed: C15.1, U6.5 (CV)
unnamed: R12.2, R14.1, U6.7 (DIS)
unnamed: C8.1, R12.1, U6.2 (TR), U6.6 (THR)

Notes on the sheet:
Range Sensor
50HZ Square Wave Output High = Digit 1 ON Low = Digit 2 ON
Digit 1 Drive
Connect Motor and Encoder to J4 or J10 but not both simultaneously
Digit 2 Drive
1K x 8

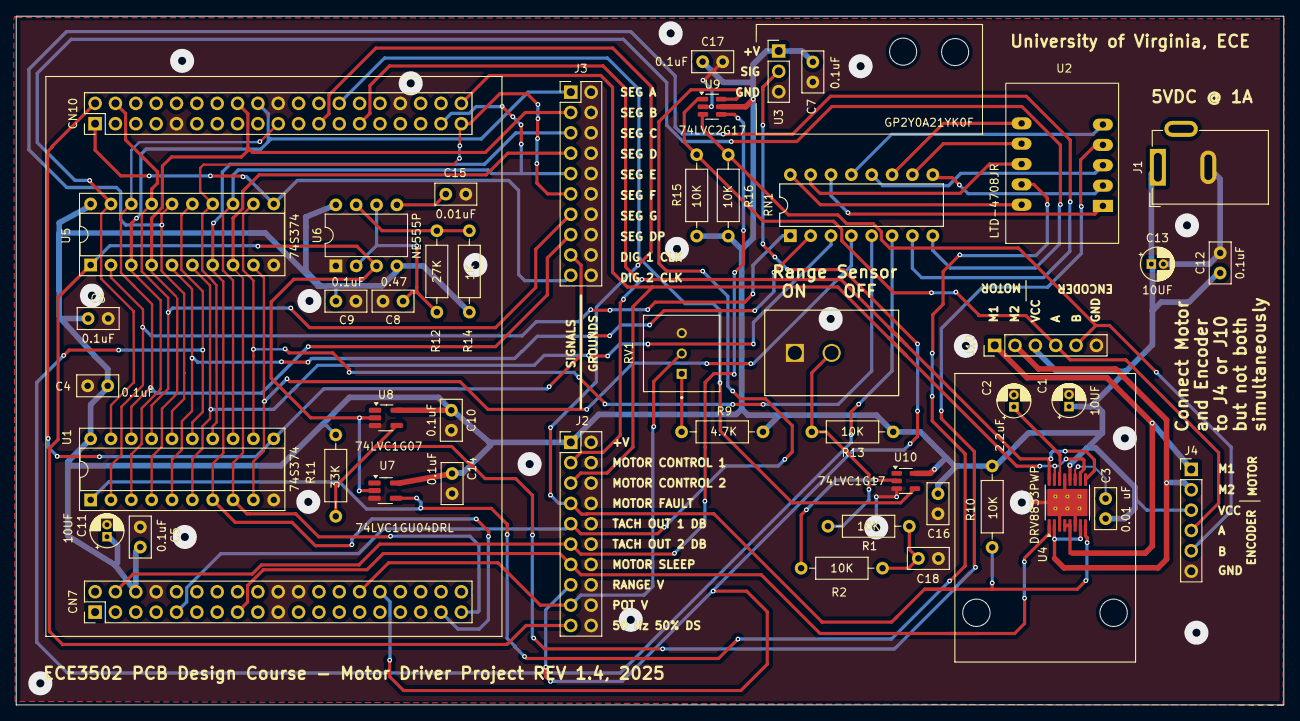
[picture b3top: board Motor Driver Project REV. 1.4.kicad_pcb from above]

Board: 2 copper layers, 158.2 x 86.0 mm, 48 parts (0 on the bottom side), 53 nets.

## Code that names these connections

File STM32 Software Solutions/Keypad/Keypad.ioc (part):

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Mcu.Name=STM32G071R(6-8-B)Tx
Mcu.Package=LQFP64
Mcu.UserName=STM32G071RBTx
PA10.Signal=GPIO_Output
PA13.Mode=Serial_Wire
PA13.Signal=SYS_SWDIO
PA14-BOOT0.Mode=Serial_Wire
PA14-BOOT0.Signal=SYS_SWCLK
PA2.Mode=Asynchronous
PA2.Signal=USART2_TX
PA3.Mode=Asynchronous
PA3.Signal=USART2_RX
PB14.Signal=GPIO_Output
PB3.Signal=GPIO_Input
PB4.Signal=GPIO_Input
PB5.Signal=GPIO_Output
PC4.Signal=GPIO_Input
PC5.Signal=GPIO_Input
RCC.HSE_VALUE=8000000
RCC.SYSCLKFreq_VALUE=16000000
board=custom

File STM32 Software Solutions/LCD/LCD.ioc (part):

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Mcu.Name=STM32G071R(6-8-B)Tx
Mcu.Package=LQFP64
Mcu.UserName=STM32G071RBTx
PA1.Mode=Full_Duplex_Master
PA1.Signal=SPI1_SCK
PA2.Mode=Full_Duplex_Master
PA2.Signal=SPI1_MOSI
PA6.Mode=Full_Duplex_Master
PA6.Signal=SPI1_MISO
PC4.Signal=GPIO_Output
PC5.Signal=GPIO_Output
PC7.Signal=GPIO_Output
RCC.HSE_VALUE=8000000
RCC.SYSCLKFreq_VALUE=16000000
board=custom

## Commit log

2025-09-23 Updated title on silkscreen
2025-09-23 Test commit
2025-09-29 Added MSPM0 outline to schematic.
2025-10-02 Added a barrel jack for connection to wall power.
2025-10-03 Added README
2025-10-03 Added Bill of Materals and reference designs
2025-10-03 Rename 12V_wall_power_datasheet.pdf to IO Component Datasheets/12V_wall_power_datasheet.pdf
2025-10-03 Added barrel jack connector
2025-10-03 Rename 3845_Web.pdf to IO Component Datasheets/Keypad_datasheet
2025-10-03 Rename Keypad_datasheet to Keypad_datasheet
2025-10-03 Rename 858_Web.pdf to IO Component Datasheets/Motor_datasheet
2025-10-03 Rename COM-09032_Web.pdf to IO Component Datasheets/Joystick_datasheet
2025-10-03 Rename ENG_DS_ALCOSWITCH_Push_Button_Switch_IPE_Series_B (1).pdf to IO Component Datasheets/ALCOSWITCH_Push_Button_Switch_datasheet
2025-10-03 Rename Microphone_datasheet.pdf to IO Component Datasheets/Microphone_datasheet.pdf
2025-10-03 Rename NHD-2.4-240320DA-CTXN.pdf to IO Component Datasheets/LCD Datasheet
2025-10-03 Rename RP_3502_datasheet.pdf to IO Component Datasheets/RP_Pushbutton_datasheet.pdf
2025-10-03 Rename SP-1504-June-2018.pdf to IO Component Datasheets/Speaker_datasheet
2025-10-03 Rename WT-1205-16-Feb-2019 (1).pdf to IO Component Datasheets/Buzzer_datasheet
2025-10-03 Rename d6.pdf to IO Component Datasheets/d6_Pushbutton_datasheet
2025-10-03 Updated spacing for headers
2025-10-03 Added Driver Datasheet
2025-10-03 Rename slau873d.pdf to IO Component Datasheets/TI_datasheet
2025-10-03 Updated formating for stm32
2025-10-03 Added motor driver to schematic
2025-10-03 Routed connections for header pins
2025-10-03 Added by-pass capacitors
2025-10-05 Added RC filter + schmitt trigger
2025-10-05 Added LDOs for 5v and 3.3v rails
2025-10-05 Added RGB led to schematic
2025-10-05 Added I2C light sensor to schematic
2025-10-05 Added footprints to motor driver circuit components
2025-10-05 Added in component for 8 bit schmitt trigger for button debouncing
2025-10-05 Formatting for pcb footprint of 8 bit schmitt trigger.
2025-10-05 Added power connection for mspm0 microcontroller
2025-10-05 Added a ground plane
2025-10-06 Formatting
2025-10-06 Updated routing for PCB
2025-10-06 Additional routing for PCB
2025-10-06 Updated button routing
2025-10-06 Updated naming on silkscreen
2025-10-06 Updated rounting
2025-10-13 Formatting change
2025-10-13 Changed caps to through-hole
2025-10-13 Added LCD connector to schematic
2025-10-13 Added power supply for LCD
2025-10-13 Completed routing for PCB
2025-10-13 Removed right angle traces
2025-10-13 Updated silk-screen
2025-10-13 Changed I2C light sensor to different type so pin spacing is not an issue
2025-10-14 Added backlight power for LCD
2025-10-14 Changed buttons to use 3.3V logic
2025-10-14 Added the buzzer driver
2025-10-14 Corrected edge cuts layer
2025-10-14 Added pin labels to the silkscreen
2025-10-14 Changed formating of silkscreen
2025-10-14 Added LCD area to the silkscreen
2025-10-14 Silkscreen formatting
2025-10-15 Backup files
2025-10-15 Corrected wiring for display for 4 SPI wire
2025-10-15 Fixed error in routing
2025-10-16 Added mic component
2025-10-16 Added correct footprint for STM board
2025-10-16 Changed to use through-hole instead of surface mount
2025-10-16 Corrected traces
2025-10-17 Made PCB smaller
2025-10-20 Moved keypads location
2025-10-20 Updated keypad location
2025-10-21 Forgot one cap that was surface mount
2025-10-21 Format fixes
2025-10-21 Generated a BOM
2025-10-21 Added bypass caps to 3.3v source
2025-10-22 Changed position of bypass capacitors
2025-10-26 Small changes
2025-10-27 Added first version of Motor Controller
2025-10-28 Updated mic to use boards 3.3v instead of development board.
2025-10-28 Finised first motor driver prototype
2025-10-30 Completed Keypad software solution
2025-11-03 Create placeholder
2025-11-06 Added minimum viable LCD code
2025-11-08 added STM32 button solution
2025-11-10 PCB update
2025-11-11 Added a second revision kicad project
2025-11-13 Added microphone code
2025-11-20 Routing for second revision of the PCB
2025-11-20 Updated routing and footprints for 2nd PCB revision
2025-11-20 Added silkscreen references
2025-11-20 Updated silkscreen
2025-11-20 Updated PCB
2025-12-01 Finished light sensor code
2025-12-03 Updates to PCB
2025-12-04 Finished joystick
